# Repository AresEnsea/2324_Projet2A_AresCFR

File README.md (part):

# 2324_Projet2A_AresCFR
## Introduction

Ce repository GitHub regroupe l'ensemble des projets & documents réalisés par l'association Ares pour la Coupe de France de Robotique 2024.

## 26/09/2023: Idées pour résoudre le problème mécanique 
### I. Partie mécanique : 

Des recherches sur internet nous on fait découvrir le Robot Trooper. 
Le site suivant permet de connaître ce robot : https://www.sick.com/fr/fr/sick-sensor-blog/trooper-le-robot-de-manutention-autonome-pour-le-distancage-en-horticulture-/w/blog-instar-robotics-success-story/

Ce deuxième site permet d'étudier la mécanique de celui-ci grâce à un concours CPGE : https://www.upsti.fr/espace-etudiants/annales-de-concours/topics/s2i-robot-trooper

Les méthodes utilisées par le robot Trooper sont:

* La récupération de pots et de cache-pots grâce à des “mains plates”. 
* Le stockage des pots grâce à un arc de cercle.

<center>

Figure 1 - Robot Trooper

</center>

## 03/10/2023: 
### II. Utilisation de capteurs de fin de course :

Idées : Positionner un capteur sur chaque côté du robot afin que le contact avec une des parois de la table permette de réinitialiser l'odométrie du robot. Par dessus, positionner une pièce imprimée en 3D pour couvrir la surface totale de chaque côté à l'instar des robots aspirateurs.  

<center>

Figure 2 - Robot Asprirateur

</center>

### III. Utilisation de capteurs TOF [Time Of Flight] :

La différence entre un capteur classique et un capteur TOF est l'état actif et passif. Le capteur classique est passif, il se comporte "comme la rétine d'un oeil". Cependant, un capteur TOF est un composant actif car il mesure un genre "d'écho" de la lumière qu'il émet (il ne mesure donc pas la lumière ambiante).
Le principe de fonctionnement de ce capteur est de mesurer le temps que met la lumière à revenir au capteur. Cela permet notamment de déterminer sa distance par rapport aux objets environnants. 

<center>

Figure 3 - Capteur TOF : Fonctionnement 
</center>

### IV. Idées de résolution du problème mécanique :

<center>

Figure 4 - Schéma explicatif de la solution mécanique 

</center>

<center>

Figure 5 - Modélisation 3D des pots à soulever (présence d'une bordure au sommet du pot) 

</center>

<center>

Figure 6 - Modélisation 3D des plantes à soulever (ne présente pas de bordure)

</center>

1) La base du robot : en forme d'entonnoir pour guider les plantes et leurs pots jusqu'à l'endroit où se situe la première pince.
2) Un ascensceur à pots : À l'endroit où l'entonnoir a le plus petit diamètre, une première pince se charge de monter les pots dans l'esapace de stockage.
3) Un espace de stockage intégré au robot : une plateforme comporte plusieurs encoches afin d'accueillir les pots.
4) Différenciation entre les pots et les plantes fragiles et résistantes : Utilisation d'un capteur de couleur pour détecter la couleur des plantes et ainsi déterminer s'il s'agit d'une plante fragile ou non. Pour détecter si le contenant stocké est un pot ou une plante, 2 capteurs de proximité seront placées à 2 hauteurs différentes : le capteur en position haute détectera les plantes et celui du bas les pots. Nous voudrions donc utiliser un capteur RFID (RFID-RC522) en haut de l'ascenseur pour savoir si c'est un pot ou une plante qui est monté par la pince. Il faut donc récupérer en premier des pots pour les stocker puis récupérer des plantes afin de les poser directement dans les pots.
5) Descente des pots contenant les plantes : Une deuxième pince est située à l'arrière du robot, elle est composée de deux plaques qui se serrent autour du pot afin de les descendre de l'espace de stockage et de les déposer sur la table. 

### IV. Servomoteur ou moteur :

Les servomoteurs respectent avec précision une position angulaire donnée. Ils ont une rotation souvent limitée à 180° et ne tournent pas en permanence alors qu'à l'inverse, les moteurs ont un mouvement continu. Les servomoteurs seront donc très utiles pour le déplacement d'un bras robotisé.

## 10/10/2023

### V. Décisions liées à la partie mécanique:

 - Dans les 6 zones de stockage deux caches-pots sont empilés. Puisque nous ne savons pas si le cache-pot sera en métal ou en impression 3D, nous choisisons de palier ce problème en adoptant la méthode suivante : dépose d'une plante dans les deux caches-pots empilés et placement dans les jardinières (comptera pour 1 point).
   
 - Première idée de stratégie pour ramasser les pots : Notre but est de récupérer des caches-pots et d'en avoir toujours en stock. Nous voulons ensuite mettre les plantes dans les caches-pots déjà stockés. Par ailleurs, si nous n'avons plus la possibilité de récupérer des caches-pots alors quelques emplacements auront un diamètre adapté à ceux des plantes fragiles. Lorsqu'il n'y aura plus de caches-pots à récupérer, nous utiliserons un capteur de couleur pour détecter si le robot prend une plante fragile ou une plante résitsante. Si la plantes est résistante alors la base du robot la poussera jusqu'à la zone de dépose des plantes. Si la plante est fragile alors elle sera stocké dans les emplacements adaptés situés dans le stockage avant de les déposer dans les jardinières.
   
 - Idée finale de stratégie pour ramasser les pots: Chaque cache-pot et chaque plante, de n'importe quel type, sera ramassé par la pince liée à l'ascenseur. Le système vérifiera quel type d'objet est encerclé par la pince. Pour chaque montée d'objet, un capteur détermine si c'est un cache-pot ou une plante (résistante ou fragile). Si c'est un cache-pot, alors il est dircetement déposé dans l'espace de stockage s'il reste un emplacement vide. Si c'est une plante fragile, alors elle est déposée dans un emplacement qui contient déjà un pot. Si c'est une plante résistante, alors elle est déposée dans un emplacement vide si c'est possible, sinon elle est déposée dans un emplacement contenant un pot.
   
 - Résolution de l'éclairement des panneaux solaires: Positionnement de deux crémaillères sur le côté du robot afin d'appuyer sur le côté du panneau solaire pour le faire tourner d'un quart de tour.
   
 -  Dépot des plantes avec leurs caches-pots dans les jardinières : Une pince est située à l'arrière du robot. À l'endroit où les pots peuvent sortir de l'espace de stockage, nous plaçons une plaque en bois posée sur des rails qui avance et recule selon une direction. Les dimensions de la plaque en bois sont : $75mm \times 75mm \times 6mm$. De plus, nous plaçons une pince à 75 mm de distance de l'espace de stockage. Celle-ci va pouvoir récupérer les pots grâce à la plaque de bois qui avance.

## 17/10/2023

### VI. Informations concernant les actionneurs 

#### VI.a Servomoteur Dynamixel AX-12 :

<center>

</center>

Caractéristiques:
- Tension de fonctionnement: 9 à 12V
- Couple décrochage (N.m) : 1,52 à 12V et 1,5A
- Vitesse hors-charge: 59 tours/minute
- Vitesse: 0,196 s/60° (à 10 Vcc)
- Température opérationnelle: -5°C à 70°C
- Vitesse de communication: 7343 bps à 1 Mbps
- Compatible avec AX-12+ à l'échelle 1:1
- Rapport de réduction: 254:1
- Poids : 54,6g
- Dimensions (mm) : 32 x 50,1 x 40

Détails :
- Fonctionnement en rotation continue ou de 0 à 300°.
- Le contrôleur de ce servomoteur permet un retour d'information de la position, de la température, du couple et de la tension d'alimentation.
- Les moteurs disposent de deux connecteurs 3 broches (cordon inclus) permettant de relier plusieurs moteurs en cascade et de les utiliser ensemble.
- Vérification de la mise à zéro grâce à deux encoches.
- Idée de code : CDR2022_23/2A/Project__Ax12/Core/main

#### VI.b Mirco Servomoteur MG90S :

<center>

</center>

Caractéristiques :
- Tension : 4,8 V - 6,0 V
- Vitesse : 0,10 s / 60 degrés
- Couple : 1,8 kg/cm (4,8 V)
- Température : -30 à +60
- Bande passante morte : 5usec

#### I.b Servomoteur SG90 :

<center>

</center>

– Dimensions : 22 x 11.5 x 27 mm
– Poids : 9 g
– Tension d’alimentation : 4.8V à 6V
– Vitesse : 0.12 s / 60° sous 4.8V
– Couple : 1.2 Kg / cm sous 4.8V
– Amplitude : de 0° à 180°

Correspondance des fils de la prise de type Graupner à 3 fils :
Marron -> GND
Rouge -> 5V
Orange -> Commande PWM

Détails : exemple de code ARDU*** : https://robotix.ah-oui.org/user_docs/dos10/sg90-datasheet.pdf

## Pendant les vacances de Novembre :

Nous nous sommes focalisés sur la mécanique du projet afin d'avoir une vision globale du robot et de ses composants que nous devrons par la suite commander.
La dernière grosse partie mécanique a concevoir est la pince avant du robot qui servira à attraper les pots et à les déposer sur la table ou dans les jardinières. Celle-ci a été réalisée grâce au logiciel fusion. 

#### Première version de la pince :
<center>

</center>

#### Deuxième version de la pince :

<center>

</center>

## 12/11/2023 :

Première version de la CAO et de l'assemblage de l'ensemble des pièces du robot (Utilisation avec modifications de certaines pièces des années précédentes et modélisation de nouvelles pièces).

Assemblage du robot : cette première version ne prend pas en compte la pince arrière car nous souhaitons d'abord être certain d'arriver à construire complètement une pince entièrement. Nous la dupliquerons par la suite pour la mettre à l'arrière du robot. 

#### Changement de l'attache de la pince à l'ascenseur :  

Création de pièces et assemblage de celles-ci avec des pièces utilisées les années passées (ex: roues/batteries/équerres) pour concevoir le robot entièrement :

<center>

</center>

## 27/11/2023:

- Finalisation de la première version de toutes les pièces du robot
- Impression de toutes les pièces afin de les tester 

## Décembre 2023:

- Modification du bord de soutien des pots. Utilisation d'une imprimante avec un plus grand plateau afin que la pièce soit imprimée en une fois pour ne pas avoir besoin de la découper en plusieurs parties. Nous avons également augmenter la hauteur de ce bord afin que la plaque en bois soit bien contrainte à rester au milieu de la pièce. Conception de pylônes de soutien. 

- Les tests de ce bord de soutien nous ont incité à agrandir son ouverture afin de laisser plus de place aux pots lors de leur sortie.  

- Création de la pièce utilisée pour faire sortir les pots de l'espace de stockage. La modification à apporter est la modification de la forme de celle-ci afin qu'elle soit identique à la forme des pots pour qu'elle soit correctement ajustée à ces derniers.  
- Nous avons également ajouté les inserts et les vis dans chaque conception afin de monter le robot entièrement.  
- Les actionneurs AX12 ont été remplacés par des petits servomoteurs SG90 pour leur taille et leur facilité de commande.

### Améliorations à réaliser:  

- Les bords du stockage sont un peu haut et certaines plantes peuvent se coincer en passant sous le stockage. La modification à apporter est sur la hauteur des piliers de soutien.
- Décaler la position de l'ascenseur pour laisser plus de place à la rotation des pots.
- Augmenter la taille de l'ascenseur pour éviter la collision entre les pots.
- Les roues ne touchent pas le sol, il faudrat donc modifier la pièce de maintien des moteurs pas à pas (correction des trous pour l'odométrie).

## Janvier 2023: 

### CAO

- Changement des actionneurs SG90 par des XL-320 pour des raisons de performance et de connectivité simplifiée.  
- L'ascenseur a été amélioré pour faciliter la rotation de la pince et a été rehaussé pour limiter la perte de pots potentiels.  
- La pince a été améliorée pour recevoir un XL-320.
- Le pousse-pot a été amélioré pour recevoir un XL-320.
- Le périmètre du robot à été réduit.

### Électronique

- Réalisation du schématique et du PCB de la carte mère du robot.
- Choix de différents capteurs de détection de pots (capteur de couleurs et de proximité).

#### Réalisation du schéma Électronique  
On commence par réaliser le schéma fonctionnel pour avoir une petite idée de l'architecture de la carte principale du robot: 

On réalise ensuite le schéma électronique avec les composants de base tout en ajoutant les composants inexistants .
Pour faciliter la lisibilité des différentes parties du schéma (conversion, communication ou encore calcul ), nous les séparons dans des blocs ou des sous-pages.

##### Partie alimentation de la carte :  

Pour cette partie nous avons repris certaines idées du schématique réalisé pour la Coupe de France de Robotique 2023 (notamment pour la partie qui concerne la batterie et le bouton d'arrêt d'urgence).
La taille du PCB a été choisie de manière à ce qu'elle puisse s'empiler avec une Raspberry Pi 4. 

De plus, nous avons du faire attention à la présence de détrompeurs sur les connecteurs et nous avons donc décidé de retirer le système anti-inversion de polarité et anti-retour de courant. De même pour le fusible de protection car il n'a jamais servi auparavant.
Nous avons par ailleurs choisi de conserver la diode TES pour les surtensions ainsi que le condensateur de filtrage.  

Comme nous l'avons décrit dans le schéma fonctionnel, nous avons besoin des tensions suivantes: 5.1V, 7.4V ainsi que du 3.3V pour les différents actionneurs. Nous allons donc devoir utiliser des convertisseurs Bucks car les 2 batteries branchées en série fournissent du 14.4V.

Remarque: Lorsque deux schémas sont similaires, afin de rendre plus lisible le schématique, nous créons des pages hiérarchiques sur lesquelles seuls les entrées et sorties apparaissent sur la page principale :

Dans ce buck, nous devons faire attention aux valeurs des résistances du pont diviseur de tension afin de délivrer la tension souhaitée [5.1V ou 7.4V].

/!\ C'est là qu'intervient la limite de l'utilisation de la page hiérarchique, car les deux bucks doivent avoir des valeurs de résitances différentes (nous n'avons pas trouvé de solution pour résoudre ce problème dans les pages hiérarchiques, bien que la solution doit exister sur des forums).  

Nous avons également choisi de mettre 2 capacités de 22uF en parrallèles afin d'avoir plus de facilités pour le soudage des composants sur le PCB (c'est également pour améliorer la qualité du routage).

La référence du pont diviseur aurait dû idéalement être mis au GND du buck pour être au plus proche afin de calculer la différence de tension et réguler la tension le mieux possible. 
Une fois les alimentations mises en place, nous rajoutons des LEDs de contrôle sur chaque tension afin de surveiller visuellement l'état des tensions. Nous rajoutons également des points de tests afin de controler les tensions avec un voltmètre.  

Nous avons par la suite réalisé la partie qui concerne les capteurs avec les différents types de communication :

Les capteurs font appels à des communications séries UART et des GPIO pour le capteur de couleur et les capteurs fin de course.  

#### Capteurs Fin de course:  

Lorsque nous appuyons sur un bouton et que nous le relâchons, un effet rebond apparaît : le microcontrolleur perçoit" plusieurs appuis/relâchements rapides.  
Pour limiter ce défaut, nous ajoutons un filtre RC qui a un objetcif de lissage. Nous ajoutons également une résistance de tirage pour éviter l'effet antenne lorsque le bouton est ouvert.  

#### UART:  

Contrairement aux années précédentes nous avons décidé d'enlever les diodes TVS anti-surtension par manque de place.  

#### Connection XL-320: 

Pour le contrôle des XL-320, le protocole fait appel à une connexion série UART half-duplex (communication dans un sens à la fois) en 5V, or la Raspberry Pi 4 utilise des UARTs full-duplex en 3.3V.

Nous utilisons donc le 74LVC2G241 pour convertir du half en full duplex (communication dans les deux sens en même temps). De plus, ce module permet de remplacer un level shifter pour adapter la tension de communication.  

#### Capteurs de couleur:
Le capteur de couleur fonctionne en 5V mais également en 3.3V, ce qui est intéréssant pour notre Raspberry qui n'accepte qu'uniquement du 3.3V.

Nous relions tous les signaux à la Raspberry (nous l'avons choisie afin d'avoir 4 UART à disposition) et nous récupèrons le 3.3V pour l'alimentation 3v3.

On finit par rajouter les GPIO non utilisés de la pi sur un bornier avec l'alimentation à coté pour pouvoir rajouter de potentiels capteurs supplémentaires.  

On lance le contrôle de règles électrique, on ajuste le schématique afin de corriger les erreurs et nous obetnons ce magnifique schéma :

(Ne pas oublier de bien référencer tous les composants hormis les small capacités, résistances et LEDs).

#### Réalisation du PCB 4 couches  
##### 1ère étape :

Il faut commencer par affecter les bonnes empreintes aux composants et les créer si elles n'existent pas.
Par exemple, tous les connecteurs JST sont référencés, cependant pour l'allimentation principale nous avons décidé de prendre des connecteurs plus gros et qui ne sont pas référencés.  

##### 2ème étape :  

On place les composants sur notre PCB en pensant à bien prendre en compte la proximité des composants (condensateurs de filtrage, résistances, ...) avec les signaux concernés et de regrouper les alimentations.  

Cela nous a "obligé" à séparer une grosse capacité en 2 petites.
Dans notre cas, la place était assez restreinte car nous ne pouvions pas mettre de condensateurs sous la carte pour éviter de percuter les composants qui se situent déjà sur la PI4.
Dans ce cas, le chevauchement de sérigraphie n'est alors plus un problème.

##### 3ème étape :

Nous devons régler différents paramètres pour définir une taille de piste et de via en fonction du courant qui passera à travers (notamment en utilisant le calculateur de kicad), ainsi que l'isolation en fonction de la tension.

On commence par placer les plans de masse et d'alimentation en fonction du placements des composants.  
Dans notre cas, nous avons choisis de faire la première couche signal/alimentation/composants/masse, deuxième plan de masse dans lequel nous nous interdisons le placement de pistes pour la laisser la plus intacte possible, et le troisième plan de puissance dans lequel nous créeons des zones 3.3v , 5.1v , 7.4v et 14.4v afin de faciliter le routage.
Nous terminons par la dernière couche qui est aussi un couche de signal/masse.

Dans l'idéal, il faudrait réaliser une cage de Faraday en mettant le plan d'allimentation et le plan de masse de part et d'autre du plan de signal. Cepandant, cela empêche toute intervention de rectification de routage après fabrication (en cas de problème).  
Nous débutons la réalisation du routage des alimentations en veillant à bien faire des grosses pistes, plusieurs vias ou bien des zones.

Enfin, nous réalisons le routage des signaux en faisant des bus de pistes pour améliorer la propreté et nous modifions le schéma lorsque c'est nécéssaire pour le "faciliter".

/!\ Éviter les pistes trop longues qui font le tour du pcb !

Il faut par la suite lancer l'analyse des règles électriques ainsi que rectifier les différents problèmes.
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
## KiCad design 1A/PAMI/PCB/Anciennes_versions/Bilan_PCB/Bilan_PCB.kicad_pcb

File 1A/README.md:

# Coupe de France de Robotique 2024 : les PAMI
> A l'occasion de la Coupe de France de Robotique 2024 : "Farming Mars", nous avons décidé de créer plusieurs PAMI (Petits Automatates Motorisés indépedants) qui devront réaliser des actions simples afin de rapporter des points à l'équipe de l'ENSEA  en assistant le robot principal. Ces PAMI doivent pouvoir se déplacer sur le plateau de la Coupe et être en mesure de détécter les robots adverses pour être homologués 

# Equipe
> L'équipe PAMI est composé de 4 élèves de 1ère année : <br>
> -Antoine Lemarignier <br>
> -Ewan Zarha Thenault <br>
> -Nathan Bainard <br>
> -Mateo Gomes <br>

# Journal de bord
>-Déroulé séance par séance

## Séance 1
>-installation machine virtuelle Ubuntu + début configuration Pi4 <br>
>-dessin du PAMI <br>
>-verification fonctionnement lidar <br>
>-utilisation github (push/pull/clone) <br>

## Séance 2
>-creation organigramme <br>
>-suite configuration machine virtuelle (configuration réseau à continuer en dehors de la séance) <br>
>-code écran (vérification) <br>
>-recherche modules récepteur émeteur 433mHz <br>

## Séance 3
>-changements schématique <br>
>-vérification moteur : fonctionnement partiel <br>

## Séance 4
>-1ère version routage <br>
>-vérification moteur : incomplet <br>

## Séance 5
>-nouvelle version pcb <br>
>-bon fonctionnement moteurs après changement de driver <br>
>-début écriture du code moteur <br>

## Séance 6
>-pcb : soudage des composants <br>

## Séance 7
>-fin soudage composants et test avec moteurs (les pcb marchent bien) <br>

## Séance 8
>-Code final qui doit fusionner le code du Lidar des roues et de l'écran <br>
>-Méca : Impression des deux autres modèles 3D pour les autres pamis <br>

## Séance 9
Après Coupe :
>-Vision : essai concluant avec tag aruco <br>
>-Complément Githhub <br>

## Séance 10
>-Derniers essais avant démonstration <br>

# Livrables
## PCB
> Présentation du schéma (grandes lignes) + PCB

## Code
> Architecture du code
> 

## Getting Started Guide
> Ici le manuel d'utilisation simple et pratique ! <br>
> Le pami fonctionne de la manière suivante : après démarrage avec le switch (allume les leds rouges),
vérifier qu'une tirette (ou un pont) est bien positionnée sur les deux pins du connecteur J102,  appuyer sur le SW NRST pour initialiser l'écran, une fois fait, le BTN2 permet de changer de stratégie parmi celles définies dans "strategy.c" dans le projet STM32CubeIDE, enfin pour démarrer le pami simplement enlever la tirette (ce qui aura pour effet de démarrer le robot après un délai de 90s ou bien appuyer sur le bouton du millieu (BTN1) pour le démarrer immédiatement.

## Rendu final
>Video ici de votre projet :
> - https://github.com/AresEnsea/2324_Projet2A_AresCFR/assets/88663397/23594f17-0ef2-46ef-a65a-15afedc95028
> - https://github.com/AresEnsea/2324_Projet2A_AresCFR/assets/88663397/61659872-7cb5-43fb-a910-f1500b88333c

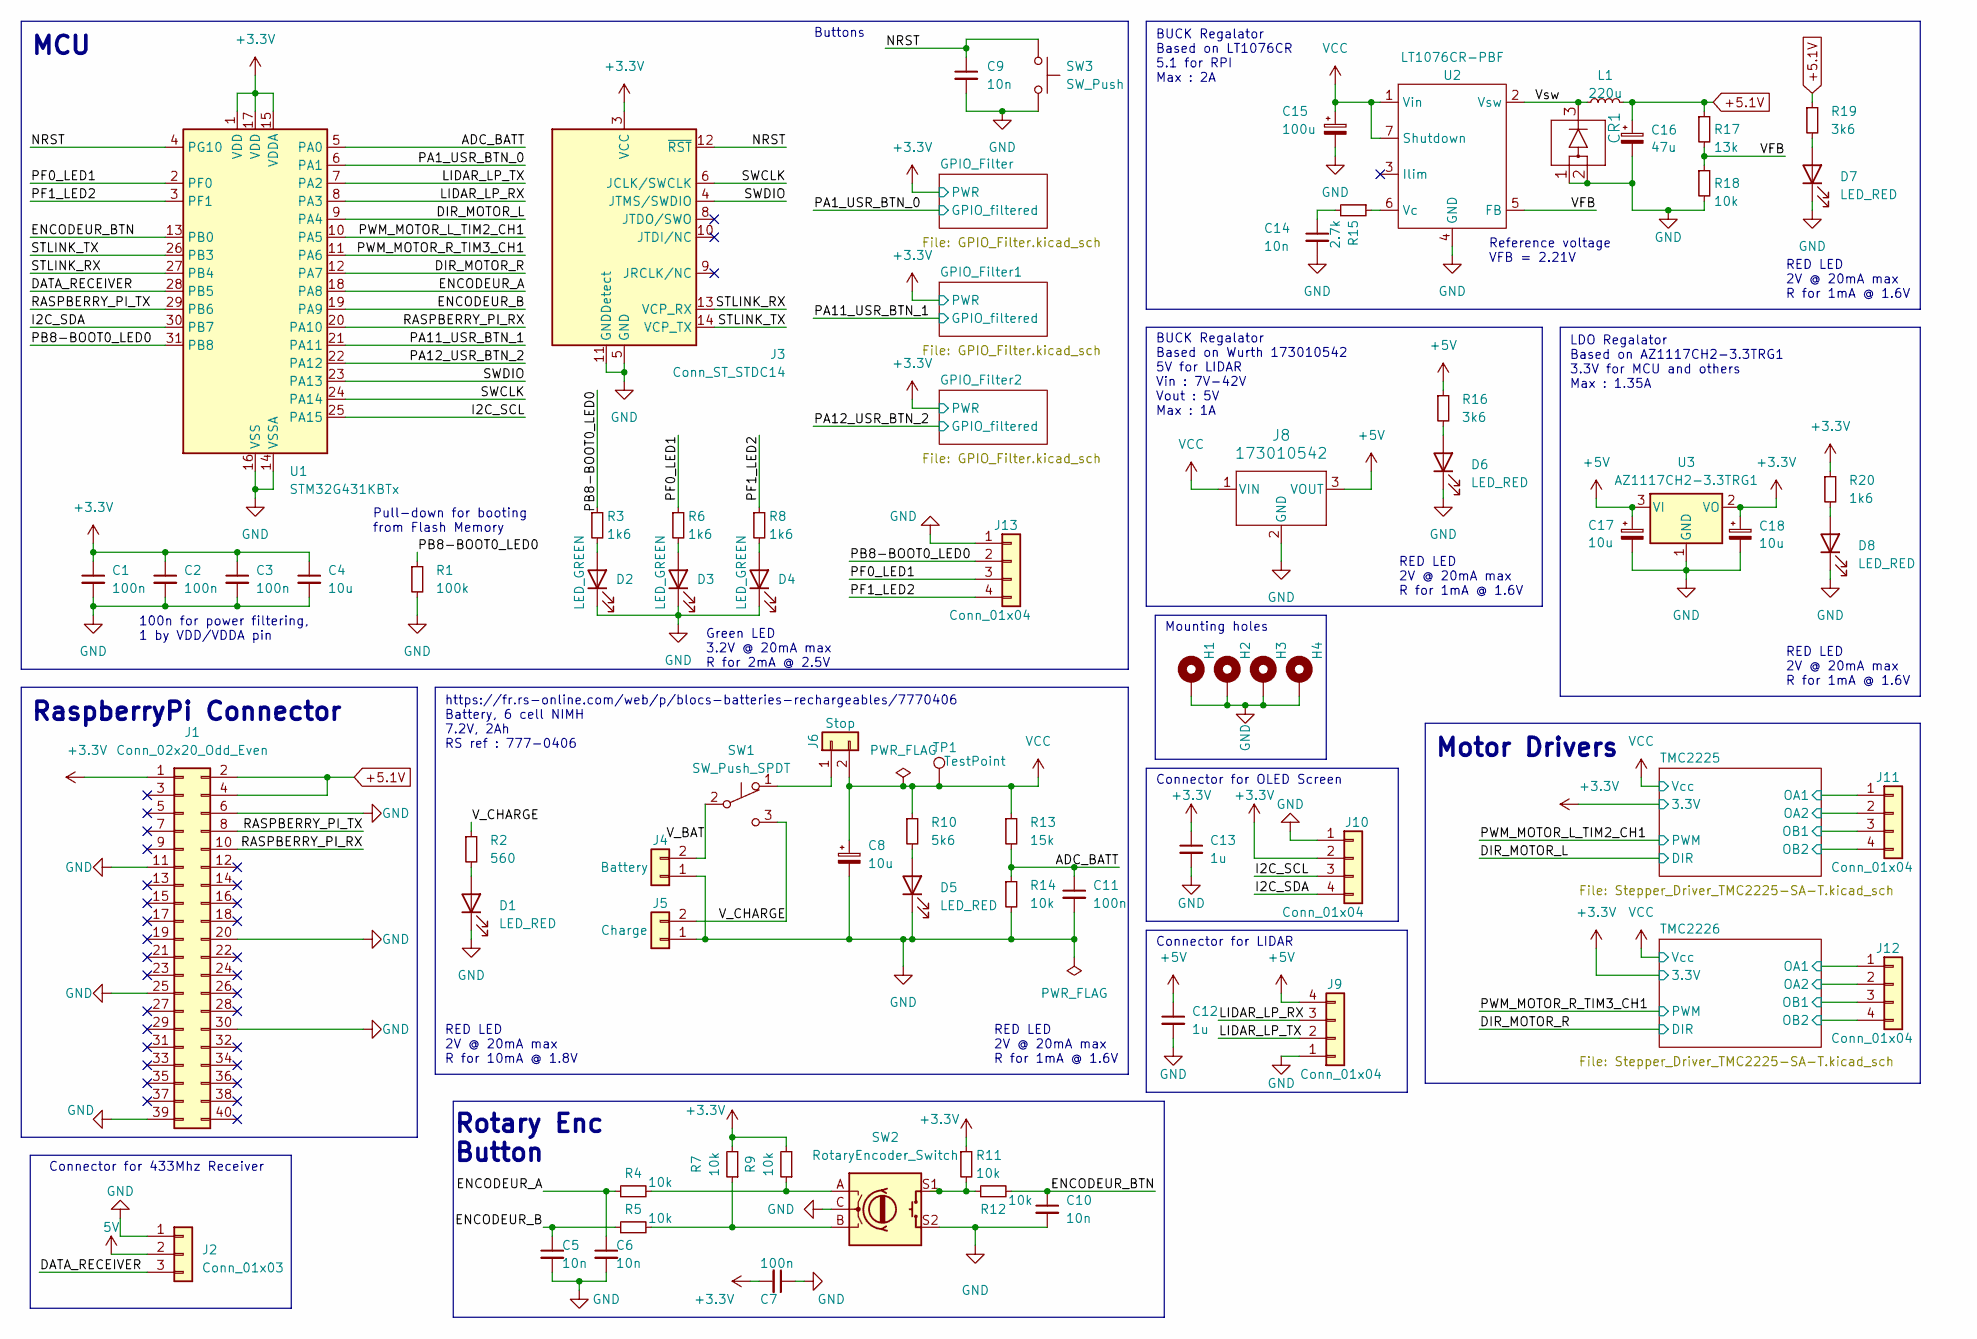
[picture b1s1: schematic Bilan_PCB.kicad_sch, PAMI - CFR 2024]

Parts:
C1, C2, C3, C7, C11: 100n; C_0402_1005Metric_Pad0.74x0.62mm_HandSolder
C4: 10u; C_0402_1005Metric_Pad0.74x0.62mm_HandSolder
C5, C6, C9, C10, C14: 10n; C_0402_1005Metric_Pad0.74x0.62mm_HandSolder
C8: 10u; CP_Elec_4x5.4; MPN 865060440001
C12, C13: 1u; C_0402_1005Metric_Pad0.74x0.62mm_HandSolder
C15: 100u; CP_Elec_6.3x7.7
C16: 47u; CP_Elec_6.3x5.4
C17, C18: 10u; CP_Elec_6.3x5.4
CR1: DST10100S; DIO_MBR1045STR
D1: LED_RED; LED_0603_1608Metric; MPN 150060RS55040
D2, D3, D4: LED_GREEN; LED_0603_1608Metric_Pad1.05x0.95mm_HandSolder
D5, D6, D7, D8: LED_RED; LED_0603_1608Metric_Pad1.05x0.95mm_HandSolder; MPN 150060RS55040
H1, H2, H3, H4: MountingHole_Pad; MountingHole_2.7mm_M2.5_DIN965_Pad
J1: Conn_02x20_Odd_Even; PinSocket_2x20_P1.00mm_Vertical_SMD
J2: Conn_01x03; JST_XH_B3B-XH-A_1x03_P2.50mm_Vertical
J3: Conn_ST_STDC14; PinHeader_2x07_P1.27mm_Vertical_SMD
J4: Battery; 691322110006; MPN 691322110002
J5: Charge; 691322110006; MPN 691322110002
J6: Stop; 691322110006; MPN 691322110002
J8: 173010542; MPN 173010542
J9, J10, J11, J12, J13: Conn_01x04; JST_XH_B4B-XH-A_1x04_P2.50mm_Vertical
L1: 220u; L_0201_0603Metric
R1: 100k; R_0402_1005Metric_Pad0.72x0.64mm_HandSolder
R2: 560; R_0402_1005Metric_Pad0.72x0.64mm_HandSolder
R3, R6, R8, R20: 1k6; R_0402_1005Metric_Pad0.72x0.64mm_HandSolder
R4, R5, R7, R9, R11, R12, R14, R18: 10k; R_0402_1005Metric_Pad0.72x0.64mm_HandSolder
R10: 5k6; R_0402_1005Metric_Pad0.72x0.64mm_HandSolder
R13: 15k; R_0402_1005Metric_Pad0.72x0.64mm_HandSolder
R15: 2.7k; R_0402_1005Metric_Pad0.72x0.64mm_HandSolder
R16, R19: 3k6; R_0402_1005Metric_Pad0.72x0.64mm_HandSolder
R17: 13k; R_0402_1005Metric_Pad0.72x0.64mm_HandSolder
SW1: SW_Push_SPDT; SW_MINI-SPDT-SW
SW2: RotaryEncoder_Switch; SW_482016514001
SW3: SW_Push; SW_PUSH_6mm
TP1: TestPoint; Pin_D0.9mm_L10.0mm_W2.4mm_FlatFork
U1: STM32G431KBTx; LQFP-32_7x7mm_P0.8mm
U2: LT1076CR-PBF; DPAK127P1394X457-8N
U3: AZ1117CH2-3.3TRG1; SOT230P700X180-4N; MPN AZ1117CH2-3.3TRG1

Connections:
+3.3V: C1.1, C2.1, C3.1, C4.1, C7.2, C13.1, C18.1, J1.1, J2.2, J3.3 (VCC), J10.2, R7.2, R9.2, R11.1, R20.1, U1.1 (VDD), U1.15 (VDDA), U1.17 (VDD), U3.2 (VO); also elsewhere on the board
+5.1V: C16.1, J1.2, J1.4, L1.2, R17.1, R19.1
+5V: C12.1, C17.1, J8.3 (VOUT), J9.4, R16.1, U3.3 (VI)
/ADC_BATT: C11.1, R13.2, R14.1, U1.5 (PA0)
/DATA_RECEIVER: J2.3, U1.28 (PB5)
/DIR_MOTOR_L: U1.9 (PA4); also elsewhere on the board
/DIR_MOTOR_R: U1.12 (PA7); also elsewhere on the board
/ENCODEUR_A: C6.1, R4.1, U1.18 (PA8)
/ENCODEUR_B: C5.1, R5.1, U1.19 (PA9)
/ENCODEUR_BTN: C10.1, R12.2, U1.13 (PB0)
/I2C_SCL: J10.3, U1.25 (PA15)
/I2C_SDA: J10.4, U1.30 (PB7)
/LIDAR_LP_RX: J9.3, U1.8 (PA3)
/LIDAR_LP_TX: J9.2, U1.7 (PA2)
/NRST: C9.1, J3.12 (~RST), SW3.1, U1.4 (PG10)
/PA1_USR_BTN_0: U1.6 (PA1); also elsewhere on the board
/PA11_USR_BTN_1: U1.21 (PA11); also elsewhere on the board
/PA12_USR_BTN_2: U1.22 (PA12); also elsewhere on the board
/PB8-BOOT0_LED0: J13.2, R1.1, R3.1, U1.31 (PB8)
/PF0_LED1: J13.3, R6.1, U1.2 (PF0)
/PF1_LED2: J13.4, R8.1, U1.3 (PF1)
/PWM_MOTOR_L_TIM2_CH1: U1.10 (PA5); also elsewhere on the board
/PWM_MOTOR_R_TIM3_CH1: U1.11 (PA6); also elsewhere on the board
/RASPBERRY_PI_RX: J1.10, U1.20 (PA10)
/RASPBERRY_PI_TX: J1.8, U1.29 (PB6)
/STLINK_RX: J3.13 (VCP_RX), U1.27 (PB4)
/STLINK_TX: J3.14 (VCP_TX), U1.26 (PB3)
/SWCLK: J3.6 (JCLK/SWCLK), U1.24 (PA14)
/SWDIO: J3.4 (JTMS/SWDIO), U1.23 (PA13)
/TMC2225/OA1: J11.1; also elsewhere on the board
/TMC2225/OA2: J11.2; also elsewhere on the board
/TMC2225/OB1: J11.3; also elsewhere on the board
/TMC2225/OB2: J11.4; also elsewhere on the board
/TMC2226/OA1: J12.1; also elsewhere on the board
/TMC2226/OA2: J12.2; also elsewhere on the board
/TMC2226/OB1: J12.3; also elsewhere on the board
/TMC2226/OB2: J12.4; also elsewhere on the board
/VFB: R17.2, R18.1, U2.5 (FB)
/V_BAT: J4.2, SW1.2 (B)
/V_CHARGE: J5.2, R2.1, SW1.3 (C)
/Vsw: CR1.3, L1.1, U2.2 (Vsw)
GND: C1.2, C2.2, C3.2, C4.2, C5.2, C6.2, C7.1, C8.2, C9.2, C10.2, C11.2, C12.2, C13.2, C14.2, C15.2, C16.2, C17.2, C18.2, CR1.1, CR1.2, D1.1 (K), D2.1 (K), D3.1 (K), D4.1 (K), D5.1 (K), D6.1 (K), D7.1 (K), D8.1 (K), H1.1, H2.1, H3.1, H4.1, J1.6, J1.11, J1.20, J1.25, J1.30, J1.39, J2.1, J3.5 (GND), J3.7 (GND), J3.11 (GNDDetect), J4.1, J5.1, J8.2 (GND), J9.1, J10.1, J13.1, R1.2, R14.2, R18.2, SW2.C, SW2.S2, SW3.2, U1.14 (VSSA), U1.16 (VSS), U1.32 (VSS), U2.4 (GND), U3.1 (GND); also elsewhere on the board
unnamed: C14.1, R15.2
unnamed: D1.2 (A), R2.2
unnamed: D2.2 (A), R3.2
unnamed: D3.2 (A), R6.2
unnamed: D4.2 (A), R8.2
unnamed: D5.2 (A), R10.2
unnamed: D6.2 (A), R16.2
unnamed: D7.2 (A), R19.2
unnamed: D8.2 (A), R20.2
unnamed: J6.1, SW1.1 (A)
unnamed: R4.2, R9.1, SW2.A
unnamed: R5.2, R7.1, SW2.B
unnamed: R11.2, R12.1, SW2.S1
unnamed: R15.1, U2.6 (Vc)
VCC: C8.1, C15.1, J6.2, J8.1 (VIN), R10.1, R13.1, TP1.1, U2.1 (Vin), U2.7 (Shutdown); also elsewhere on the board

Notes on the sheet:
Rotary Enc Button
BUCK Regalator Based on Wurth 173010542 5V for LIDAR Vin : 7V-42V Vout : 5V Max : 1A
RED LED 2V @ 20mA max R for 1mA @ 1.6V
MCU
Motor Drivers
Mounting holes
LDO Regalator Based on AZ1117CH2-3.3TRG1 3.3V for MCU and others Max : 1.35A
RaspberryPi Connector
100n for power filtering, 1 by VDD/VDDA pin
Reference voltage VFB = 2.21V
Green LED 3.2V @ 20mA max R for 2mA @ 2.5V
Connector for 433Mhz Receiver
Buttons
BUCK Regalator Based on LT1076CR 5.1 for RPI Max : 2A
RED LED 2V @ 20mA max R for 10mA @ 1.8V
Connector for LIDAR
Connector for OLED Screen
Pull-down for booting from Flash Memory
https://fr.rs-online.com/web/p/blocs-batteries-rechargeables/7770406 Battery, 6 cell NIMH 7.2V, 2Ah RS ref : 777-0406

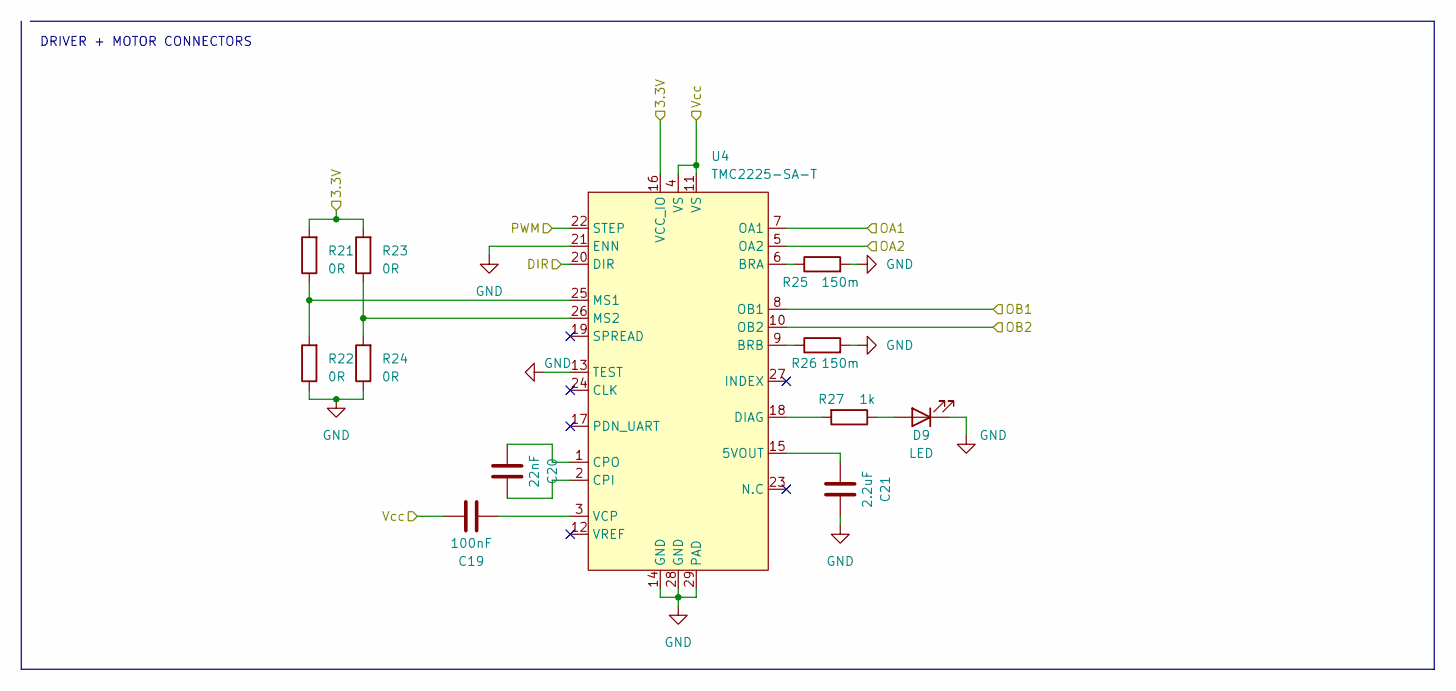
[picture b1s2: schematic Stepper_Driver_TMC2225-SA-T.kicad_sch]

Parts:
C19: 100nF; C_0603_1608Metric_Pad1.08x0.95mm_HandSolder
C20: 22nF; C_0603_1608Metric_Pad1.08x0.95mm_HandSolder
C21: 2.2uF; C_0805_2012Metric_Pad1.18x1.45mm_HandSolder
D9: LED; LED_0603_1608Metric_Pad1.05x0.95mm_HandSolder
R21, R22, R23, R24: 0R; R_0603_1608Metric_Pad0.98x0.95mm_HandSolder
R25, R26: 150m; R_1206_3216Metric_Pad1.30x1.75mm_HandSolder
R27: 1k; R_0603_1608Metric_Pad0.98x0.95mm_HandSolder
U4: TMC2225-SA-T; HTSSOP-28-1EP_4.4x9.7mm_P0.65mm_EP2.85x5.4mm_ThermalVias

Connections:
+3.3V: R21.2, R23.2, U4.16 (VCC_IO); also elsewhere on the board
/DIR_MOTOR_L: U4.20 (DIR); also elsewhere on the board
/PWM_MOTOR_L_TIM2_CH1: U4.22 (STEP); also elsewhere on the board
/TMC2225/OA1: U4.7 (OA1); also elsewhere on the board
/TMC2225/OA2: U4.5 (OA2); also elsewhere on the board
/TMC2225/OB1: U4.8 (OB1); also elsewhere on the board
/TMC2225/OB2: U4.10 (OB2); also elsewhere on the board
GND: C21.1, D9.1 (K), R22.1, R24.1, R25.2, R26.2, U4.13 (TEST), U4.14 (GND), U4.21 (ENN), U4.28 (GND), U4.29 (PAD); also elsewhere on the board
unnamed: D9.2 (A), R27.1
unnamed: C21.2, U4.15 (5VOUT)
unnamed: R25.1, U4.6 (BRA)
unnamed: R26.1, U4.9 (BRB)
unnamed: C20.1, U4.2 (CPI)
unnamed: C20.2, U4.1 (CPO)
unnamed: R27.2, U4.18 (DIAG)
unnamed: R21.1, R22.2, U4.25 (MS1)
unnamed: R23.1, R24.2, U4.26 (MS2)
unnamed: C19.2, U4.3 (VCP)
VCC: C19.1, U4.4 (VS), U4.11 (VS); also elsewhere on the board

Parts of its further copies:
C22: 100nF; C_0603_1608Metric_Pad1.08x0.95mm_HandSolder
C23: 22nF; C_0603_1608Metric_Pad1.08x0.95mm_HandSolder
C24: 2.2uF; C_0805_2012Metric_Pad1.18x1.45mm_HandSolder
D10: LED; LED_0603_1608Metric_Pad1.05x0.95mm_HandSolder
R28, R29, R30, R31: 0R; R_0603_1608Metric_Pad0.98x0.95mm_HandSolder
R32, R33: 150m; R_1206_3216Metric_Pad1.30x1.75mm_HandSolder
R34: 1k; R_0603_1608Metric_Pad0.98x0.95mm_HandSolder
U5: TMC2225-SA-T; HTSSOP-28-1EP_4.4x9.7mm_P0.65mm_EP2.85x5.4mm_ThermalVias

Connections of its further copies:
+3.3V: R28.2, R30.2, U5.16 (VCC_IO); also elsewhere on the board
/DIR_MOTOR_R: U5.20 (DIR); also elsewhere on the board
/PWM_MOTOR_R_TIM3_CH1: U5.22 (STEP); also elsewhere on the board
/TMC2226/OA1: U5.7 (OA1); also elsewhere on the board
/TMC2226/OA2: U5.5 (OA2); also elsewhere on the board
/TMC2226/OB1: U5.8 (OB1); also elsewhere on the board
/TMC2226/OB2: U5.10 (OB2); also elsewhere on the board
GND: C24.1, D10.1 (K), R29.1, R31.1, R32.2, R33.2, U5.13 (TEST), U5.14 (GND), U5.21 (ENN), U5.28 (GND), U5.29 (PAD); also elsewhere on the board
unnamed: D10.2 (A), R34.1
unnamed: C24.2, U5.15 (5VOUT)
unnamed: R32.1, U5.6 (BRA)
unnamed: R33.1, U5.9 (BRB)
unnamed: C23.1, U5.2 (CPI)
unnamed: C23.2, U5.1 (CPO)
unnamed: R34.2, U5.18 (DIAG)
unnamed: R28.1, R29.2, U5.25 (MS1)
unnamed: R30.1, R31.2, U5.26 (MS2)
unnamed: C22.2, U5.3 (VCP)
VCC: C22.1, U5.4 (VS), U5.11 (VS); also elsewhere on the board

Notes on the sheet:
DRIVER + MOTOR CONNECTORS

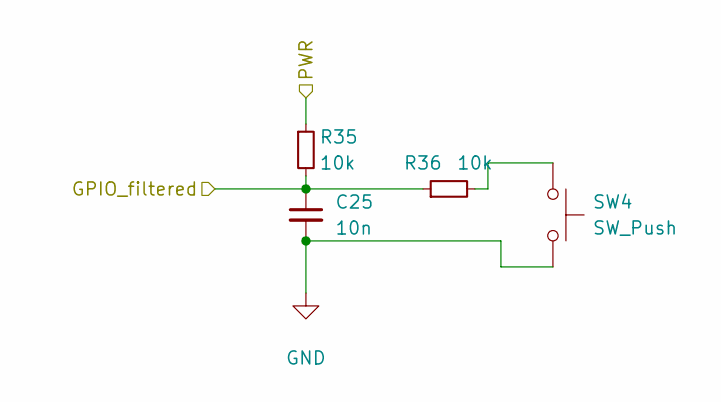
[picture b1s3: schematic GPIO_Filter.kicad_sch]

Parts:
C25: 10n; C_0402_1005Metric_Pad0.74x0.62mm_HandSolder
R35, R36: 10k; R_0402_1005Metric_Pad0.72x0.64mm_HandSolder
SW4: SW_Push; SW_PUSH_6mm

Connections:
+3.3V: R35.1; also elsewhere on the board
/PA1_USR_BTN_0: C25.1, R35.2, R36.1; also elsewhere on the board
GND: C25.2, SW4.2; also elsewhere on the board
unnamed: R36.2, SW4.1

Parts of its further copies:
C26, C27: 10n; C_0402_1005Metric_Pad0.74x0.62mm_HandSolder
R37, R38, R39, R40: 10k; R_0402_1005Metric_Pad0.72x0.64mm_HandSolder
SW5, SW6: SW_Push; SW_PUSH_6mm

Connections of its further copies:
+3.3V: R37.1, R39.1; also elsewhere on the board
/PA11_USR_BTN_1: C26.1, R37.2, R38.1; also elsewhere on the board
/PA12_USR_BTN_2: C27.1, R39.2, R40.1; also elsewhere on the board
GND: C26.2, C27.2, SW5.2, SW6.2; also elsewhere on the board
unnamed: R38.2, SW5.1
unnamed: R40.2, SW6.1

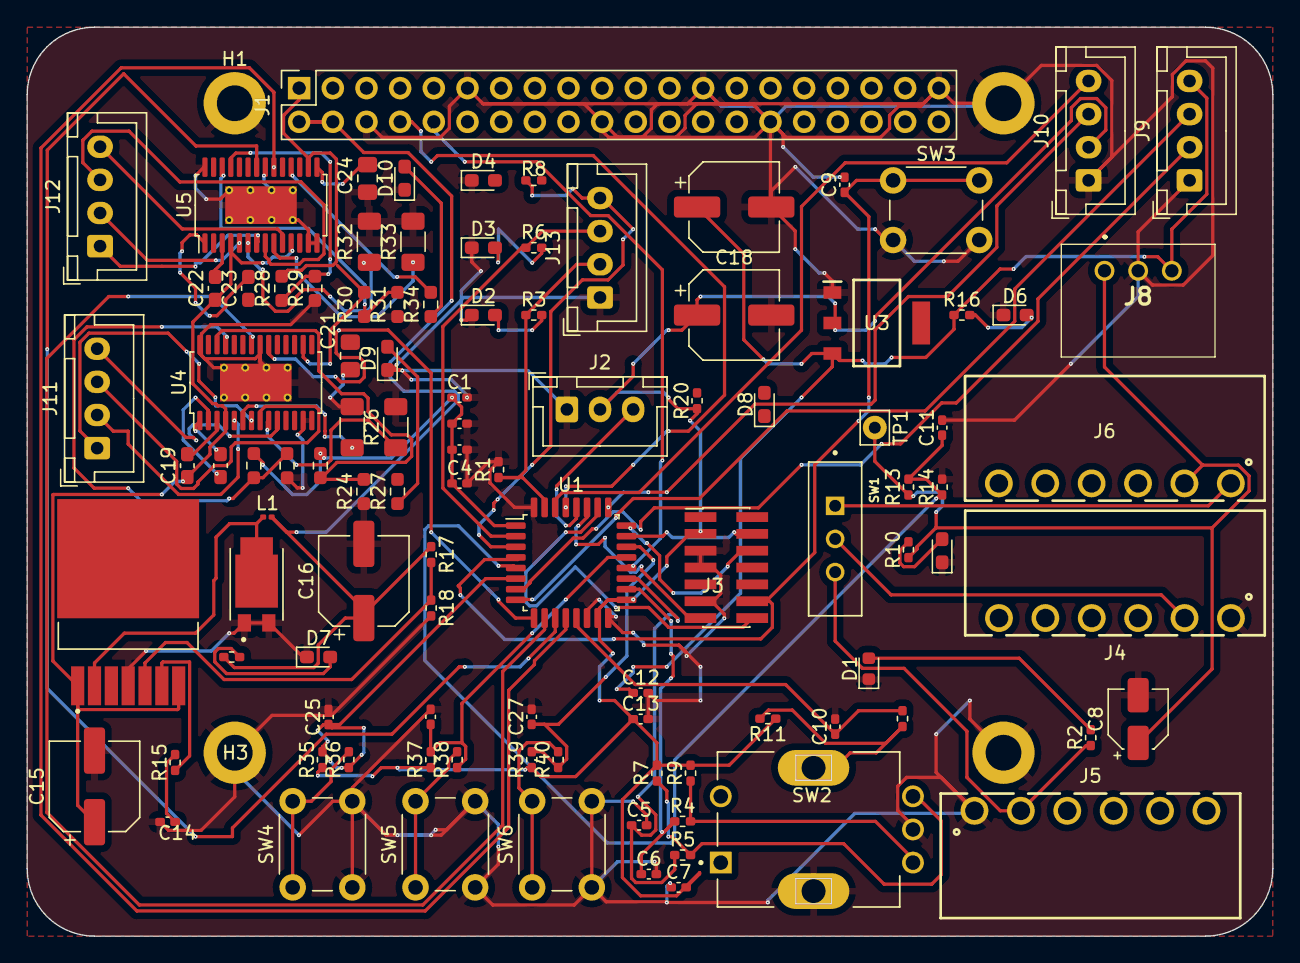
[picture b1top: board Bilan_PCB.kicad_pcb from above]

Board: 2 copper layers, 94.0 x 68.6 mm, 107 parts (0 on the bottom side), 80 nets.

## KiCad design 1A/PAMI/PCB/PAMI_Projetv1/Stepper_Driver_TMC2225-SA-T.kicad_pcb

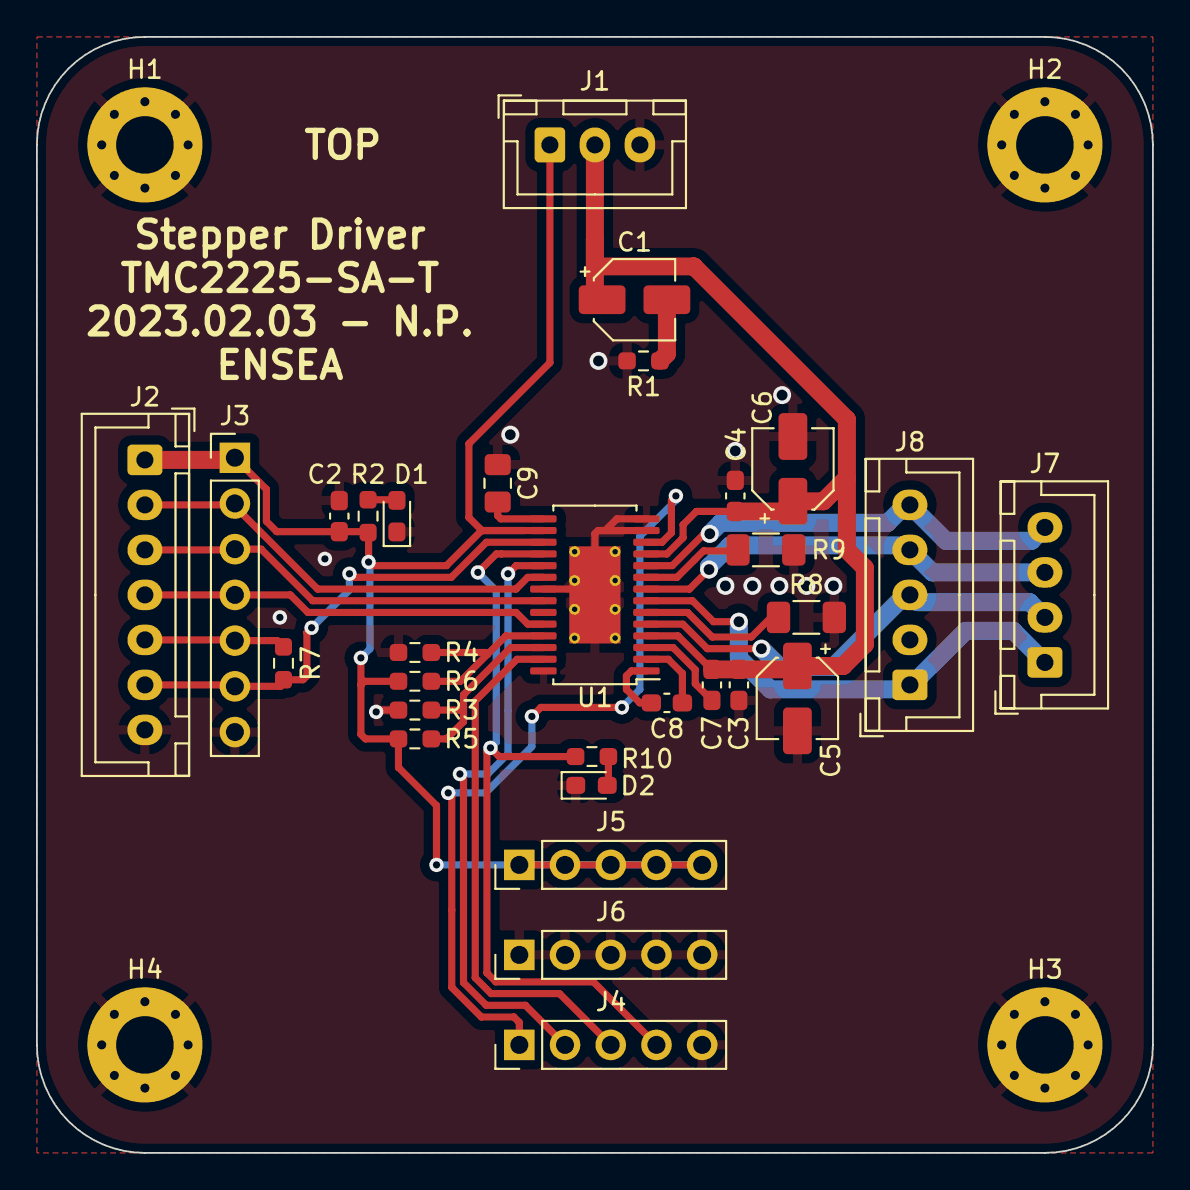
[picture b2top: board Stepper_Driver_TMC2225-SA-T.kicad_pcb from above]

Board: 2 copper layers, 62.0 x 62.0 mm, 34 parts (0 on the bottom side), 27 nets.

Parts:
C1, C5, C6: 10uF; CP_Elec_4x5.7
C2, C3, C4, C7: 100nF; C_0603_1608Metric_Pad1.08x0.95mm_HandSolder
C8: 22nF; C_0603_1608Metric_Pad1.08x0.95mm_HandSolder
C9: 2.2uF; C_0805_2012Metric_Pad1.18x1.45mm_HandSolder
D1, D2: LED; LED_0603_1608Metric_Pad1.05x0.95mm_HandSolder
H1, H2, H3, H4: MountingHole_Pad; MountingHole_3.2mm_M3_Pad_Via
J1: Conn_01x03_Male; JST_XH_B3B-XH-A_1x03_P2.50mm_Vertical
J2: Conn_01x07; JST_XH_B7B-XH-A_1x07_P2.50mm_Vertical
J3: Conn_01x07; PinHeader_1x07_P2.54mm_Vertical
J4, J5, J6: Conn_01x05; PinHeader_1x05_P2.54mm_Vertical
J7: Conn_01x04_Female; JST_XH_B4B-XH-A_1x04_P2.50mm_Vertical
J8: Conn_01x05_Female; JST_XH_B5B-XH-A_1x05_P2.50mm_Vertical
R1: 110m; R_0603_1608Metric_Pad0.98x0.95mm_HandSolder
R2, R7, R10: 1k; R_0603_1608Metric_Pad0.98x0.95mm_HandSolder
R3, R4, R5, R6: 0R; R_0603_1608Metric_Pad0.98x0.95mm_HandSolder
R8, R9: 150m; R_1206_3216Metric_Pad1.30x1.75mm_HandSolder
U1: TMC2225-SA-T; HTSSOP-28-1EP_4.4x9.7mm_P0.65mm_EP2.85x5.4mm_ThermalVias

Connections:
5VOUT: C9.2, U1.15 (5VOUT)
+3.3V: C2.1, J1.1, J2.1, J3.1, J5.1, J5.2, J5.3, J5.4, J5.5, R2.1, R3.2, R5.2, U1.16 (VCC_IO)
BRA: R8.1, U1.6 (BRA)
BRB: R9.1, U1.9 (BRB)
CLK: J2.4, J3.4, U1.24 (CLK)
DIAG: J4.4, R10.2, U1.18 (DIAG)
DIR: J2.2, J3.2, U1.20 (DIR)
GND: C2.2, C3.2, C4.2, C5.2, C6.2, C9.1, D1.1 (K), D2.1 (K), H1.1, H2.1, H3.1, H4.1, J1.3, J2.7, J3.7, J4.5, J6.1, J6.2, J6.3, J6.4, J6.5, R1.2, R4.1, R6.1, R8.2, R9.2, U1.13 (TEST), U1.14 (GND), U1.21 (ENN), U1.28 (GND), U1.29 (PAD)
INDEX: J4.3, U1.27 (INDEX)
MS1: R3.1, R4.2, U1.25 (MS1)
MS2: R5.1, R6.2, U1.26 (MS2)
unnamed: C1.2, R1.1
unnamed: C8.1, U1.2 (CPI)
unnamed: C8.2, U1.1 (CPO)
unnamed: D1.2 (A), R2.2
unnamed: D2.2 (A), R10.1
OA1: J7.1, J8.1, U1.7 (OA1)
OA2: J7.2, J8.3, U1.5 (OA2)
OB1: J7.3, J8.4, U1.8 (OB1)
OB2: J7.4, J8.5, U1.10 (OB2)
SPREAD: J4.2, U1.19 (SPREAD)
STEP: J2.3, J3.3, U1.22 (STEP)
UART_RX: J2.6, J3.6, R7.1, U1.17 (PDN_UART)
UART_TX: J2.5, J3.5, R7.2
VCC: C1.1, C3.1, C4.1, C5.1, C6.1, C7.1, J1.2, U1.4 (VS), U1.11 (VS)
VCP: C7.2, U1.3 (VCP)
VREF: J4.1, U1.12 (VREF)

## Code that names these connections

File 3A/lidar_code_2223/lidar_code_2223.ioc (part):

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Mcu.Name=STM32G070RBTx
Mcu.Package=LQFP64
Mcu.UserName=STM32G070RBTx
PA10.Mode=I2C
PA10.Signal=I2C1_SDA
PA11\ [PA9].Signal=GPIO_Output
PA12\ [PA10].Signal=GPIO_Output
PA15.Signal=GPIO_Output
PA4.Signal=GPIO_Output
PA5.Signal=GPIO_Output
PA7.Signal=GPIO_Output
PA8.Signal=GPIO_Output
PA9.Mode=I2C
PA9.Signal=I2C1_SCL
PB0.Signal=GPIO_Output
PB1.Signal=GPIO_Output
PB10.Signal=GPIO_Output
PB11.Signal=GPIO_Output
PB13.Signal=GPIO_Output
PB14.Signal=GPIO_Output
PB3.Signal=GPIO_Output
PB4.Signal=GPIO_Output
PB6.Signal=GPIO_Output
PB7.Signal=GPIO_Output
PB9.Signal=GPIO_Output
PC0.Signal=GPIO_Output
PC10.Signal=GPIO_Output
PC12.Signal=GPIO_Output
PC13.Signal=GPIO_Output
PC15-OSC32_OUT\ (PC15).Signal=GPIO_Output
PC2.Signal=GPIO_Output
PC3.Signal=GPIO_Output
PC4.Signal=GPIO_Output
PC7.Signal=GPIO_Output
PC9.Signal=GPIO_Output
PD0.Signal=GPIO_Output
PD2.Signal=GPIO_Output
PD3.Signal=GPIO_Output
PD5.Mode=Asynchronous
PD5.Signal=USART2_TX
PD6.Mode=Asynchronous
PD6.Signal=USART2_RX
PD8.Signal=GPIO_Output
PF0-OSC_IN\ (PF0).Mode=HSE-External-Oscillator
PF0-OSC_IN\ (PF0).Signal=RCC_OSC_IN
PF1-OSC_OUT\ (PF1).Mode=HSE-External-Oscillator
PF1-OSC_OUT\ (PF1).Signal=RCC_OSC_OUT
RCC.HSE_VALUE=16000000
RCC.SYSCLKFreq_VALUE=64000000
RCC.SYSCLKSource=RCC_SYSCLKSOURCE_PLLCLK
board=custom

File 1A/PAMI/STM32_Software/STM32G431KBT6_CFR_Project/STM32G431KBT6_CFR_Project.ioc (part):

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Mcu.Name=STM32G431K(6-8-B)Tx
Mcu.Package=LQFP32
Mcu.UserName=STM32G431KBTx
PA0.GPIOParameters=GPIO_Label
PA0.GPIO_Label=ADC_BATT
PA0.Mode=IN1-Single-Ended
PA0.Signal=ADC1_IN1
PA1.GPIOParameters=GPIO_Label,GPIO_ModeDefaultEXTI
PA1.GPIO_Label=USR_BTN_0
PA1.GPIO_ModeDefaultEXTI=GPIO_MODE_IT_FALLING
PA1.Signal=GPXTI1
PA10.GPIOParameters=GPIO_Label
PA10.GPIO_Label=LIDAR_RX
PA10.Mode=Asynchronous
PA10.Signal=USART1_RX
PA11.GPIOParameters=GPIO_Label,GPIO_ModeDefaultEXTI
PA11.GPIO_Label=USR_BTN_2
PA11.GPIO_ModeDefaultEXTI=GPIO_MODE_IT_FALLING
PA11.Signal=GPXTI11
PA12.GPIOParameters=GPIO_Label,GPIO_ModeDefaultEXTI
PA12.GPIO_Label=USR_BTN_1
PA12.GPIO_ModeDefaultEXTI=GPIO_MODE_IT_FALLING
PA12.Signal=GPXTI12
PA13.Mode=Serial_Wire
PA13.Signal=SYS_JTMS-SWDIO
PA14.Mode=Serial_Wire
PA14.Signal=SYS_JTCK-SWCLK
PA15.GPIOParameters=GPIO_Speed,GPIO_Label
PA15.GPIO_Label=I2C_SCL_OLED
PA15.GPIO_Speed=GPIO_SPEED_FREQ_VERY_HIGH
PA15.Mode=I2C
PA15.Signal=I2C1_SCL
PA2.GPIOParameters=GPIO_Label
PA2.GPIO_Label=RPI_TX
PA2.Mode=Asynchronous
PA2.Signal=LPUART1_TX
PA3.GPIOParameters=GPIO_Label
PA3.GPIO_Label=RPI_RX
PA3.Mode=Asynchronous
PA3.Signal=LPUART1_RX
PA4.GPIOParameters=GPIO_Label
PA4.GPIO_Label=DIR_MOTOR_R
PA4.Signal=GPIO_Output
PA5.GPIOParameters=GPIO_Label
PA5.GPIO_Label=PWM_MOTOR_R
PA5.Signal=S_TIM2_CH1
PA6.GPIOParameters=GPIO_Label
PA6.GPIO_Label=PWM_MOTOR_L
PA6.Signal=S_TIM3_CH1
PA7.GPIOParameters=GPIO_Label
PA7.GPIO_Label=DIR_MOTOR_L
PA7.Signal=GPIO_Output
PA8.GPIOParameters=GPIO_Label
PA8.GPIO_Label=TIM1_CH1_ENC
PA8.Signal=S_TIM1_CH1
PA9.GPIOParameters=GPIO_Label
PA9.GPIO_Label=TIM1_CH2_ENC
PA9.Signal=S_TIM1_CH2
PB0.GPIOParameters=GPIO_Label,GPIO_ModeDefaultEXTI
PB0.GPIO_Label=ENC_BTN
PB0.GPIO_ModeDefaultEXTI=GPIO_MODE_IT_FALLING
PB0.Signal=GPXTI0
PB3.GPIOParameters=GPIO_Label
PB3.GPIO_Label=VCP_TX
PB3.Mode=Asynchronous
PB3.Signal=USART2_TX
PB4.GPIOParameters=GPIO_Label
PB4.GPIO_Label=VCP_RX
PB4.Mode=Asynchronous
PB4.Signal=USART2_RX
PB5.GPIOParameters=GPIO_PuPd,GPIO_Label,GPIO_ModeDefaultEXTI
PB5.GPIO_Label=START
PB5.GPIO_ModeDefaultEXTI=GPIO_MODE_IT_FALLING
PB5.GPIO_PuPd=GPIO_PULLDOWN
PB5.Signal=GPXTI5
PB6.GPIOParameters=GPIO_Label
PB6.GPIO_Label=LIDAR_TX
PB6.Mode=Asynchronous
PB6.Signal=USART1_TX
PB7.GPIOParameters=GPIO_Speed,GPIO_Label
PB7.GPIO_Label=I2C_SDA_OLED
PB7.GPIO_Speed=GPIO_SPEED_FREQ_VERY_HIGH
PB7.Mode=I2C
PB7.Signal=I2C1_SDA
PB8-BOOT0.GPIOParameters=GPIO_Label
PB8-BOOT0.GPIO_Label=LED0
PB8-BOOT0.Signal=GPIO_Output
PF0-OSC_IN.GPIOParameters=GPIO_Label
PF0-OSC_IN.GPIO_Label=LED1
PF0-OSC_IN.Signal=GPIO_Output
PF1-OSC_OUT.GPIOParameters=GPIO_Label
PF1-OSC_OUT.GPIO_Label=LED2
PF1-OSC_OUT.Signal=GPIO_Output
RCC.HSE_VALUE=8000000
RCC.SYSCLKFreq_VALUE=170000000
RCC.SYSCLKSource=RCC_SYSCLKSOURCE_PLLCLK
board=custom

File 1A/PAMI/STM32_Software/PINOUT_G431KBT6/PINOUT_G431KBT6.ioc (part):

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Mcu.Name=STM32G431K(6-8-B)Tx
Mcu.Package=LQFP32
Mcu.UserName=STM32G431KBTx
PA0.Mode=IN1-Single-Ended
PA0.Signal=ADC1_IN1
PA1.GPIOParameters=GPIO_Label
PA1.GPIO_Label=USR_BTN_0
PA1.Signal=GPXTI1
PA10.Mode=Asynchronous
PA10.Signal=USART1_RX
PA11.GPIOParameters=GPIO_Label
PA11.GPIO_Label=USR_BTN_1
PA11.Signal=GPXTI11
PA12.GPIOParameters=GPIO_Label
PA12.GPIO_Label=USR_BTN_2
PA12.Signal=GPXTI12
PA13.Mode=Serial_Wire
PA13.Signal=SYS_JTMS-SWDIO
PA14.Mode=Serial_Wire
PA14.Signal=SYS_JTCK-SWCLK
PA15.Mode=I2C
PA15.Signal=I2C1_SCL
PA2.Mode=Asynchronous
PA2.Signal=LPUART1_TX
PA3.Mode=Asynchronous
PA3.Signal=LPUART1_RX
PA4.GPIOParameters=GPIO_Label
PA4.GPIO_Label=TIM2_DIR
PA4.Signal=GPIO_Output
PA5.Signal=S_TIM2_CH1
PA6.Signal=S_TIM3_CH1
PA7.GPIOParameters=GPIO_Label
PA7.GPIO_Label=TIM3_DIR
PA7.Signal=GPIO_Output
PA8.Signal=S_TIM1_CH1
PA9.Signal=S_TIM1_CH2
PB0.GPIOParameters=GPIO_Label
PB0.GPIO_Label=ENC_BTN
PB0.Signal=GPXTI0
PB3.Mode=Asynchronous
PB3.Signal=USART2_TX
PB4.Mode=Asynchronous
PB4.Signal=USART2_RX
PB6.Mode=Asynchronous
PB6.Signal=USART1_TX
PB7.Mode=I2C
PB7.Signal=I2C1_SDA
PB8-BOOT0.GPIOParameters=GPIO_Label
PB8-BOOT0.GPIO_Label=LED0
PB8-BOOT0.Signal=GPIO_Output
PF0-OSC_IN.GPIOParameters=GPIO_Label
PF0-OSC_IN.GPIO_Label=LED1
PF0-OSC_IN.Signal=GPIO_Output
PF1-OSC_OUT.GPIOParameters=GPIO_Label
PF1-OSC_OUT.GPIO_Label=LED2
PF1-OSC_OUT.Signal=GPIO_Output
PG10-NRST.GPIOParameters=GPIO_Label
PG10-NRST.GPIO_Label=LED3
PG10-NRST.Signal=GPIO_Output
RCC.HSE_VALUE=8000000
RCC.SYSCLKFreq_VALUE=16000000
board=custom

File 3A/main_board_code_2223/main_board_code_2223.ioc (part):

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Mcu.Name=STM32F446R(C-E)Tx
Mcu.Package=LQFP64
Mcu.UserName=STM32F446RETx
PA0-WKUP.Mode=Asynchronous
PA0-WKUP.Signal=UART4_TX
PA1.Mode=Asynchronous
PA1.Signal=UART4_RX
PA10.Mode=Asynchronous
PA10.Signal=USART1_RX
PA2.Mode=Asynchronous
PA2.Signal=USART2_TX
PA3.Mode=Asynchronous
PA3.Signal=USART2_RX
PA5.GPIOParameters=GPIO_Label
PA5.GPIO_Label=GREEN_LED
PA5.Signal=GPIO_Output
PA6.GPIOParameters=GPIO_Label
PA6.GPIO_Label=L_ENCODER_A
PA6.Signal=S_TIM3_CH1
PA7.GPIOParameters=GPIO_Label
PA7.GPIO_Label=L_ENCODER_B
PA7.Signal=S_TIM3_CH2
PA8.GPIOParameters=GPIO_Label
PA8.GPIO_Label=R_ENCODER_A
PA8.Signal=S_TIM1_CH1
PA9.GPIOParameters=GPIO_Label
PA9.GPIO_Label=R_ENCODER_B
PA9.Signal=S_TIM1_CH2
PB0.GPIOParameters=GPIO_Label
PB0.GPIO_Label=WIFI
PB0.Signal=GPIO_Input
PB6.Mode=Asynchronous
PB6.Signal=USART1_TX
PB8.GPIOParameters=GPIO_Label
PB8.GPIO_Label=TEAM_LED
PB8.Signal=GPIO_Output
PB9.Signal=S_TIM11_CH1
PC0.GPIOParameters=GPIO_Label
PC0.GPIO_Label=L_MOTOR_EN
PC0.Signal=GPIO_Output
PC1.GPIOParameters=GPIO_Label
PC1.GPIO_Label=R_MOTOR_EN
PC1.Signal=GPIO_Output
PC11.GPIOParameters=GPIO_Label
PC11.GPIO_Label=R_MOTOR_DIR
PC11.Signal=GPIO_Output
PC12.Mode=Asynchronous
PC12.Signal=UART5_TX
PC2.GPIOParameters=GPIO_Label
PC2.GPIO_Label=L_MOTOR_DIR
PC2.Signal=GPIO_Output
PC6.Mode=Asynchronous
PC6.Signal=USART6_TX
PC7.Mode=Asynchronous
PC7.Signal=USART6_RX
PC8.GPIOParameters=GPIO_PuPd,GPIO_Label
PC8.GPIO_Label=START
PC8.GPIO_PuPd=GPIO_PULLDOWN
PC8.Signal=GPIO_Input
PC9.Signal=S_TIM8_CH4
PD2.Mode=Asynchronous
PD2.Signal=UART5_RX
RCC.HSE_VALUE=8000000
RCC.SYSCLKFreq_VALUE=180000000
RCC.SYSCLKSource=RCC_SYSCLKSOURCE_PLLCLK
board=NUCLEO-F446RE
boardIOC=true
